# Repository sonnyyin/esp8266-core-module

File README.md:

# esp8266-core-module
a tiny esp8266 wifi module designed with kicad. 

This is a esp8266 core module designed with kicad 6.0, for reduce the pcb size when you use relay.

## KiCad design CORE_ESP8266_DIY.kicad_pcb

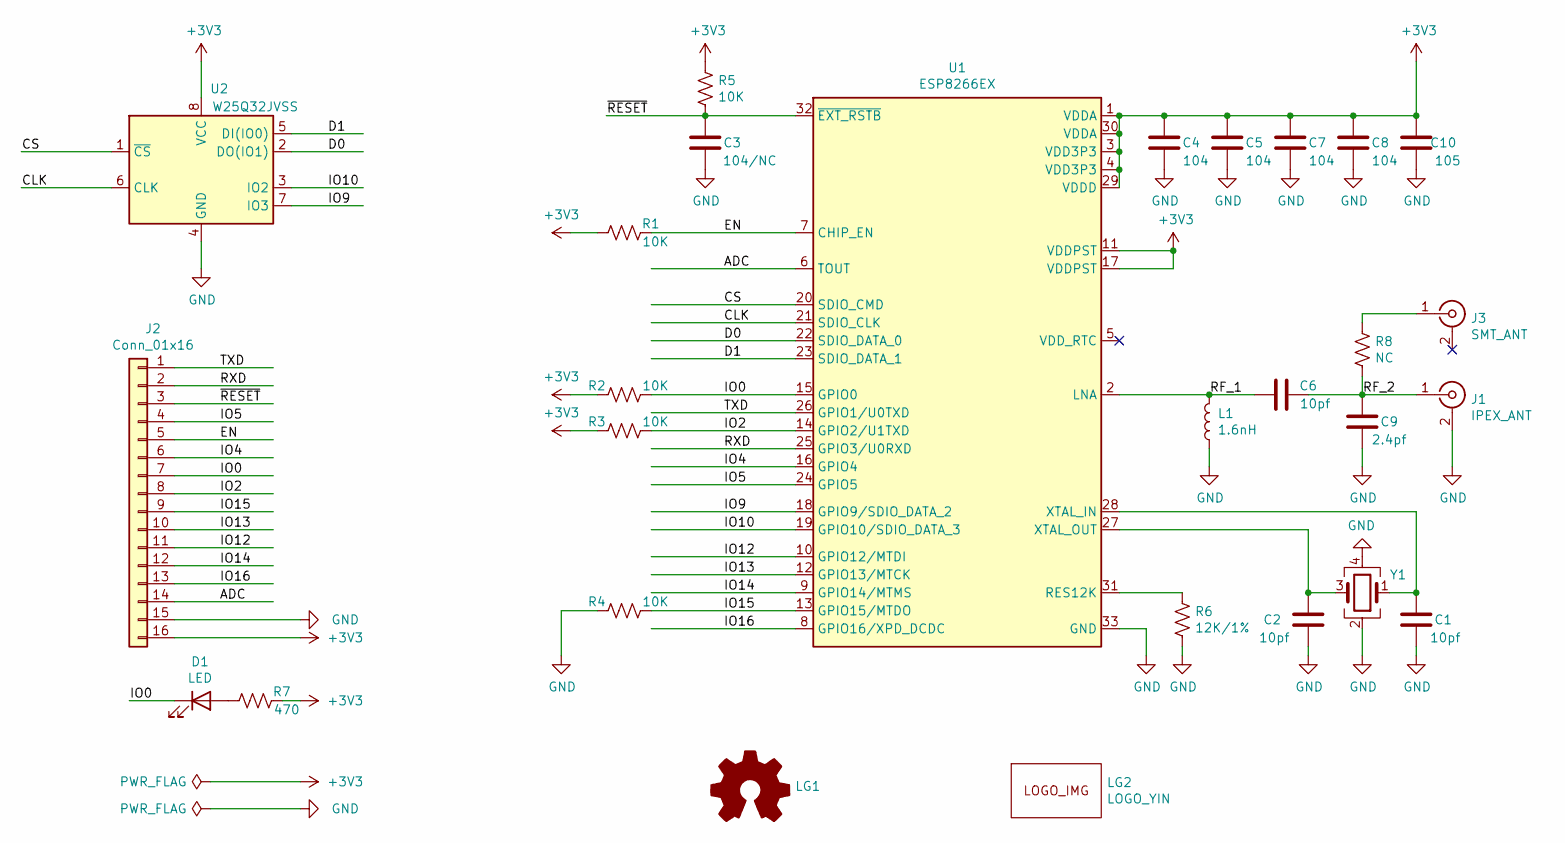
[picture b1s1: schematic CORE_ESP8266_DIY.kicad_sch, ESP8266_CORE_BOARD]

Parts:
C1, C2, C6: 10pf; CAP_0402
C3: 104/NC; CAP_0402
C4, C5, C7, C8: 104; CAP_0402
C9: 2.4pf; CAP_0402
C10: 105; CAP_0402
D1: LED; LED_0402_1005Metric
J1: IPEX_ANT; U.FL_Hirose_U.FL-R-SMT-1_Vertical
J2: Conn_01x16; PinHeader_1x16_P1.00mm_Horizontal_Edge
J3: SMT_ANT; ANT_AN9520
L1: 1.6nH; L_0402
LG1: Logo_Open_Hardware_Small; OSHW-Logo2_9.8x8mm_SilkScreen
LG2: LOGO_YIN; LOGO_YIN_10X3.5MM
R1, R2, R3, R4, R5: 10K; RES_0402
R6: 12K/1%; RES_0402
R7: 470; RES_0402
R8: NC; RES_0402
U1: ESP8266EX; QFN-32-1EP_5x5mm_P0.5mm_EP3.45x3.45mm_ThermalVias
U2: W25Q32JVSS; SOIC-8_5.23x5.23mm_P1.27mm
Y1: 26MHz/10ppm; Crystal_SMD_3225-4Pin_3.2x2.5mm

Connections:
+3V3: C4.2, C5.2, C7.2, C8.2, C10.2, J2.16, R1.1, R2.1, R3.1, R5.1, R7.2, U1.1 (VDDA), U1.3 (VDD3P3), U1.4 (VDD3P3), U1.11 (VDDPST), U1.17 (VDDPST), U1.29 (VDDD), U1.30 (VDDA), U2.8 (VCC)
/ADC: J2.14, U1.6 (TOUT)
/CLK: U1.21 (SDIO_CLK), U2.6 (CLK)
/CS: U1.20 (SDIO_CMD), U2.1 (~CS)
/D0: U1.22 (SDIO_DATA_0), U2.2 (DO(IO1))
/D1: U1.23 (SDIO_DATA_1), U2.5 (DI(IO0))
/EN: J2.5, R1.2, U1.7 (CHIP_EN)
/IO0: D1.1 (K), J2.7, R2.2, U1.15 (GPIO0)
/IO2: J2.8, R3.2, U1.14 (GPIO2/U1TXD)
/IO4: J2.6, U1.16 (GPIO4)
/IO5: J2.4, U1.24 (GPIO5)
/IO9: U1.18 (GPIO9/SDIO_DATA_2), U2.7 (IO3)
/IO10: U1.19 (GPIO10/SDIO_DATA_3), U2.3 (IO2)
/IO12: J2.11, U1.10 (GPIO12/MTDI)
/IO13: J2.10, U1.12 (GPIO13/MTCK)
/IO14: J2.12, U1.9 (GPIO14/MTMS)
/IO15: J2.9, R4.2, U1.13 (GPIO15/MTDO)
/IO16: J2.13, U1.8 (GPIO16/XPD_DCDC)
/RF_1: C6.2, L1.2, U1.2 (LNA)
/RF_2: C6.1, C9.2, J1.1 (In), R8.2
/RXD: J2.2, U1.25 (GPIO3/U0RXD)
/TXD: J2.1, U1.26 (GPIO1/U0TXD)
/~RESET: C3.2, J2.3, R5.2, U1.32 (~EXT_RSTB)
GND: C1.1, C2.1, C3.1, C4.1, C5.1, C7.1, C8.1, C9.1, C10.1, J1.2 (Ext), J2.15, L1.1, R4.1, R6.2, U1.33 (GND), U2.4 (GND), Y1.2, Y1.4
unnamed: C1.2, U1.28 (XTAL_IN), Y1.1
unnamed: C2.2, U1.27 (XTAL_OUT), Y1.3
unnamed: D1.2 (A), R7.1
unnamed: J3.1 (In), R8.1
unnamed: R6.1, U1.31 (RES12K)

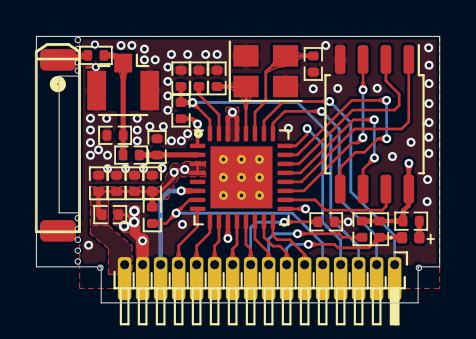
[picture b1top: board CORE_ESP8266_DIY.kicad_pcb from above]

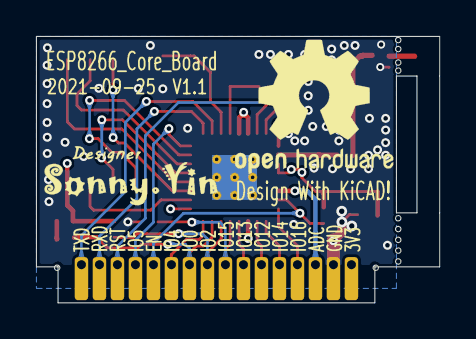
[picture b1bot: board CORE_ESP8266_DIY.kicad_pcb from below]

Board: 4 copper layers, 22.4 x 14.8 mm, 28 parts (2 on the bottom side), 29 nets.

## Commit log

2022-12-07 Add files via upload
    upload V1.1 design
